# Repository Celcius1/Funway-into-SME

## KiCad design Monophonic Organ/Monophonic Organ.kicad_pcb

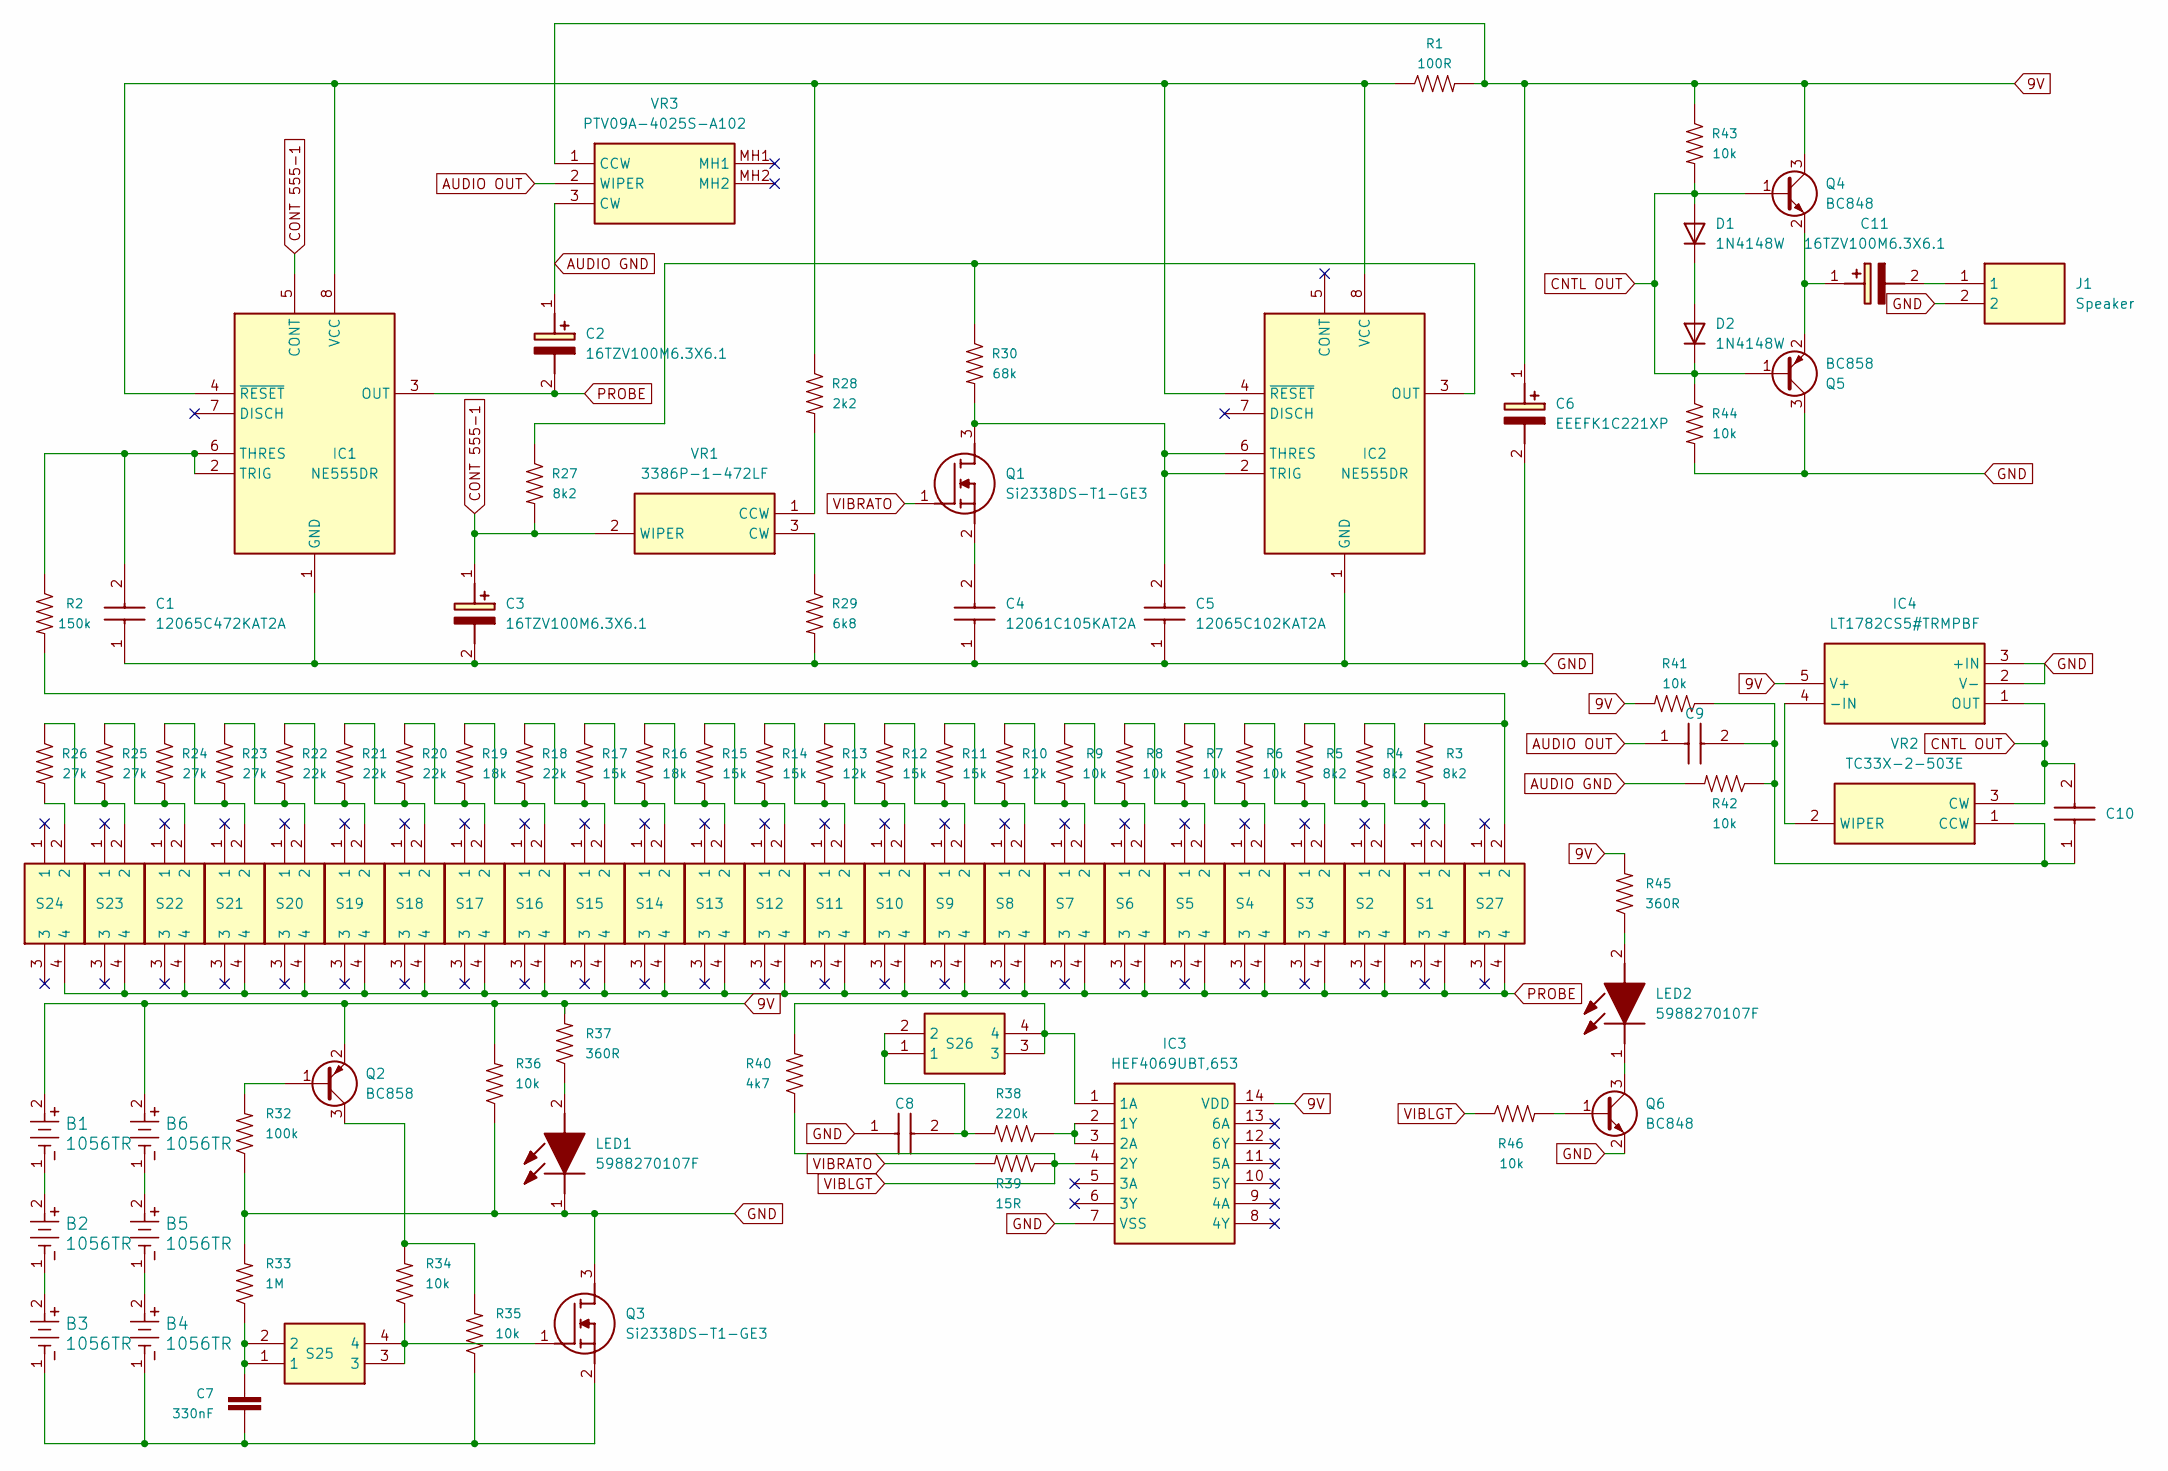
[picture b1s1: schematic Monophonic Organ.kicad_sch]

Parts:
B1, B2, B3, B4, B5, B6: 1056TR
C1: 12065C472KAT2A; CAPC3216X94N; Manufacturer_Part_Number 12065C472KAT2A
C2, C3, C11: 16TZV100M6.3X6.1; 16TZV100M63X61; Manufacturer_Part_Number 16TZV100M6.3X6.1
C4, C9: 12061C105KAT2A; CAPC3216X229N; Manufacturer_Part_Number 12061C105KAT2A
C5: 12065C102KAT2A; CAPC3216X94N; Manufacturer_Part_Number 12065C102KAT2A
C6: EEEFK1C221XP; EEE0JA331XP; Manufacturer_Part_Number EEEFK1C221XP
C7: 330nF; C_1206_3216Metric
C8: 12061C473KAT2A; CAPC3216X94N; Manufacturer_Part_Number 12061C473KAT2A
C10: 12065A150JAT2A; CAPC3216X94N; Manufacturer_Part_Number 12065A150JAT2A
D1, D2: 1N4148W; D_SOD-123
IC1, IC2: NE555DR; SOIC127P600X175-8N; Manufacturer_Part_Number NE555DR; Mouser Part Number 595-NE555DR
IC3: HEF4069UBT,653; SOIC127P600X175-14N; Manufacturer_Part_Number HEF4069UBT,653
IC4: LT1782CS5#TRMPBF; SOT95P280X100-5N; Manufacturer_Part_Number LT1782CS5#TRMPBF
J1: Speaker; 17761192; Manufacturer_Part_Number 1776119-2
LED1, LED2: 5988270107F; Manufacturer_Part_Number 5988270107F
Q1, Q3: Si2338DS-T1-GE3; SOT95P237X112-3N; Manufacturer_Part_Number Si2338DS-T1-GE3
Q2, Q5: BC858; SOT-23
Q4, Q6: BC848; SOT-23
R1: 100R; R_1206_3216Metric
R2: 150k; R_1206_3216Metric
R3, R4, R5, R27: 8k2; R_1206_3216Metric
R6, R7, R8, R9, R34, R35, R36, R41, R42, R43, R44, R46: 10k; R_1206_3216Metric
R10, R13: 12k; R_1206_3216Metric
R11, R12, R14, R15, R17: 15k; R_1206_3216Metric
R16, R19: 18k; R_1206_3216Metric
R18, R20, R21, R22: 22k; R_1206_3216Metric
R23, R24, R25, R26: 27k; R_1206_3216Metric
R28: 2k2; R_1206_3216Metric
R29: 6k8; R_1206_3216Metric
R30: 68k; R_1206_3216Metric
R32: 100k; R_1206_3216Metric
R33: 1M; R_1206_3216Metric
R37, R45: 360R; R_1206_3216Metric
R38: 220k; R_1206_3216Metric
R39: 15R; R_1206_3216Metric
R40: 4k7; R_1206_3216Metric
S1, S2, S3, S4, S5, S6, S7, S8, S9, S10, S11, S12, S13, S14, S15, S16, S17, S18, S19, S20, S21, S22, S23, S24, S25, S26, S27: FSM4JSMATR; Manufacturer_Part_Number FSM4JSMATR
VR1: 3386P-1-472LF; 3386P_1; Manufacturer_Part_Number 3386P-1-472LF
VR2: TC33X-2-503E; TC33X2503E; Manufacturer_Part_Number TC33X-2-503E
VR3: PTV09A-4025S-A102; PTV09A4025SA102; Manufacturer_Part_Number PTV09A-4025S-A102

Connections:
9V: B1.2, B6.2, C6.1 (+), IC3.14 (VDD), IC4.5 (V+), Q2.2 (E), Q4.3 (C), R1.2, R36.2, R37.2, R41.2, R43.1, R45.2, VR3.1 (CCW)
AUDIO GND: C2.1 (+), R42.2, VR3.3 (CW)
AUDIO OUT: C9.1, VR3.2 (WIPER)
CNTL OUT: C10.2, D1.2 (A), D2.1 (K), IC4.1 (OUT), Q4.1 (B), Q5.1 (B), R43.2, R44.1, VR2.3 (CW)
CONT 555-1: C3.1 (+), IC1.5 (CONT), R27.2, VR1.2 (WIPER)
GND: C1.1, C3.2 (-), C4.1, C5.1, C6.2 (-), C8.1, IC1.1 (GND), IC2.1 (GND), IC3.7 (VSS), IC4.2 (V-), IC4.3 (+IN), J1.2, LED1.1 (K), Q3.3 (D), Q5.3 (C), Q6.2 (E), R29.2, R32.1, R33.2, R36.1, R44.2
unnamed: B1.1, B2.2
unnamed: B2.1, B3.2
unnamed: B4.2, B5.1
unnamed: B5.2, B6.1
unnamed: C7.2, R33.1, S25.1, S25.2
unnamed: C8.2, R38.2, S26.1, S26.2
unnamed: C11.1 (+), Q4.2 (E), Q5.2 (E)
unnamed: C11.2 (-), J1.1
unnamed: D1.1 (K), D2.2 (A)
unnamed: C1.2, IC1.2 (TRIG), IC1.6 (THRES), R2.1
unnamed: IC1.4 (~RESET), IC1.8 (VCC), IC2.4 (~RESET), IC2.8 (VCC), R1.1, R28.1
unnamed: IC2.3 (OUT), R27.1, R30.1
unnamed: C5.2, IC2.2 (TRIG), IC2.6 (THRES), Q1.3 (D), R30.2
unnamed: IC3.1 (1A), R40.2, S26.3, S26.4
unnamed: IC3.2 (1Y), IC3.3 (2A), R38.1
unnamed: IC4.4 (-IN), VR2.2 (WIPER)
unnamed: LED1.2 (A), R37.1
unnamed: LED2.2 (A), R45.1
unnamed: LED2.1 (K), Q6.3 (C)
unnamed: C4.2, Q1.2 (S)
unnamed: Q2.1 (B), R32.2
unnamed: Q2.3 (C), R34.2, R35.2
unnamed: Q3.1 (G), R34.1, S25.3, S25.4
unnamed: B3.1, B4.1, C7.1, Q3.2 (S), R35.1
unnamed: Q6.1 (B), R46.2
unnamed: R2.2, R3.1, S27.2
unnamed: R3.2, R4.1, S1.2
unnamed: R4.2, R5.1, S2.2
unnamed: R5.2, R6.1, S3.2
unnamed: R6.2, R7.1, S4.2
unnamed: R7.2, R8.1, S5.2
unnamed: R8.2, R9.1, S6.2
unnamed: R9.2, R10.1, S7.2
unnamed: R10.2, R11.1, S8.2
unnamed: R11.2, R12.1, S9.2
unnamed: R12.2, R13.1, S10.2
unnamed: R13.2, R14.1, S11.2
unnamed: R14.2, R15.1, S12.2
unnamed: R15.2, R16.1, S13.2
unnamed: R16.2, R17.1, S14.2
unnamed: R17.2, R18.1, S15.2
unnamed: R18.2, R19.1, S16.2
unnamed: R19.2, R20.1, S17.2
unnamed: R20.2, R21.1, S18.2
unnamed: R21.2, R22.1, S19.2
unnamed: R22.2, R23.1, S20.2
unnamed: R23.2, R24.1, S21.2
unnamed: R24.2, R25.1, S22.2
unnamed: R25.2, R26.1, S23.2
unnamed: R26.2, S24.2
unnamed: R28.2, VR1.1 (CCW)
unnamed: R29.1, VR1.3 (CW)
unnamed: C9.2, C10.1, R41.1, R42.1, VR2.1 (CCW)
PROBE: C2.2 (-), IC1.3 (OUT), S1.4, S2.4, S3.4, S4.4, S5.4, S6.4, S7.4, S8.4, S9.4, S10.4, S11.4, S12.4, S13.4, S14.4, S15.4, S16.4, S17.4, S18.4, S19.4, S20.4, S21.4, S22.4, S23.4, S24.4, S27.4
VIBLGT: IC3.4 (2Y), R39.1, R40.1, R46.1
VIBRATO: Q1.1 (G), R39.2

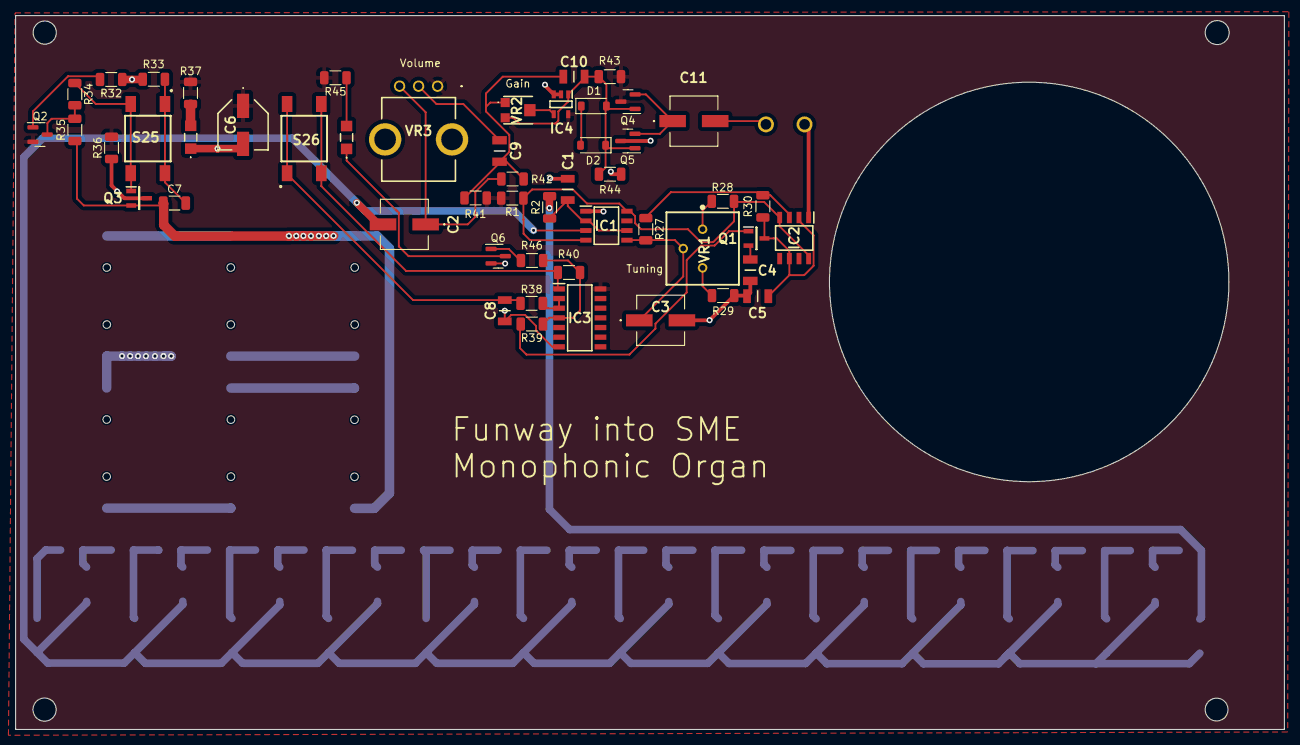
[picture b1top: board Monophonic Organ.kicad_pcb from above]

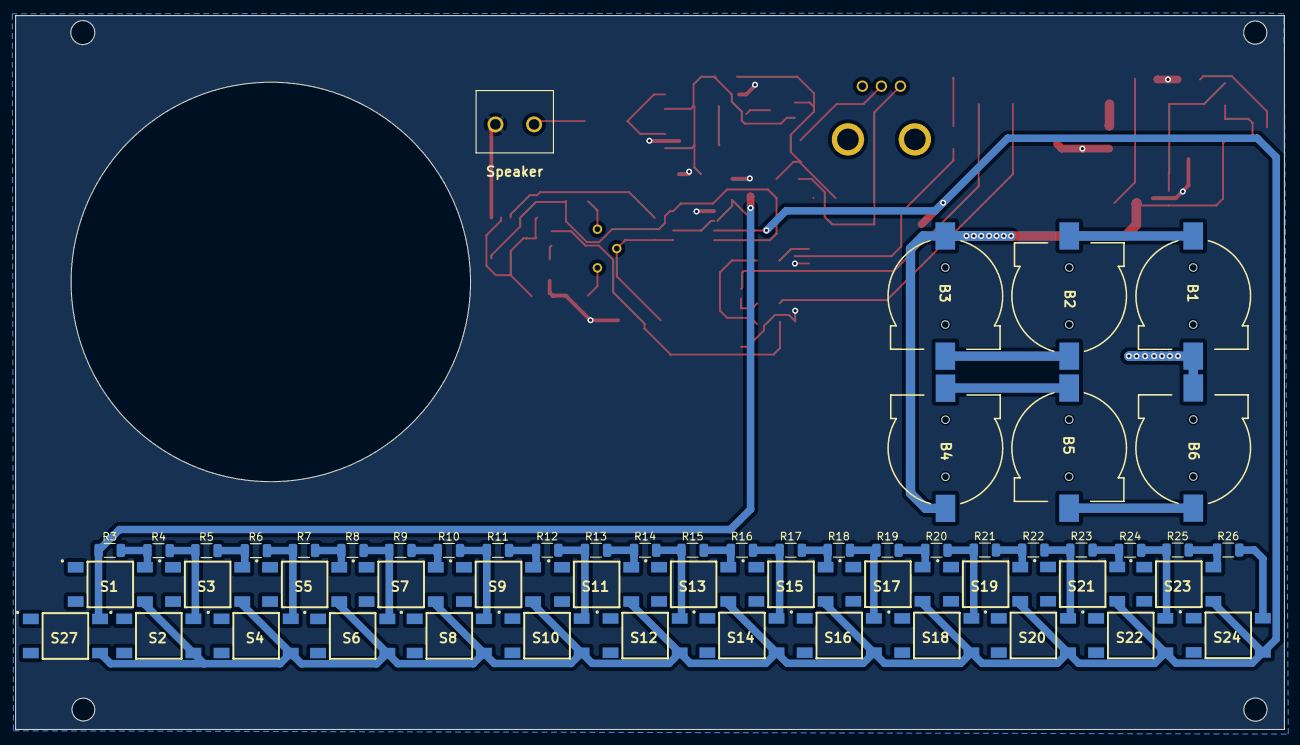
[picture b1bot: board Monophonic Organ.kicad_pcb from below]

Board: 2 copper layers, 166.9 x 93.9 mm, 107 parts (56 on the bottom side), 62 nets.

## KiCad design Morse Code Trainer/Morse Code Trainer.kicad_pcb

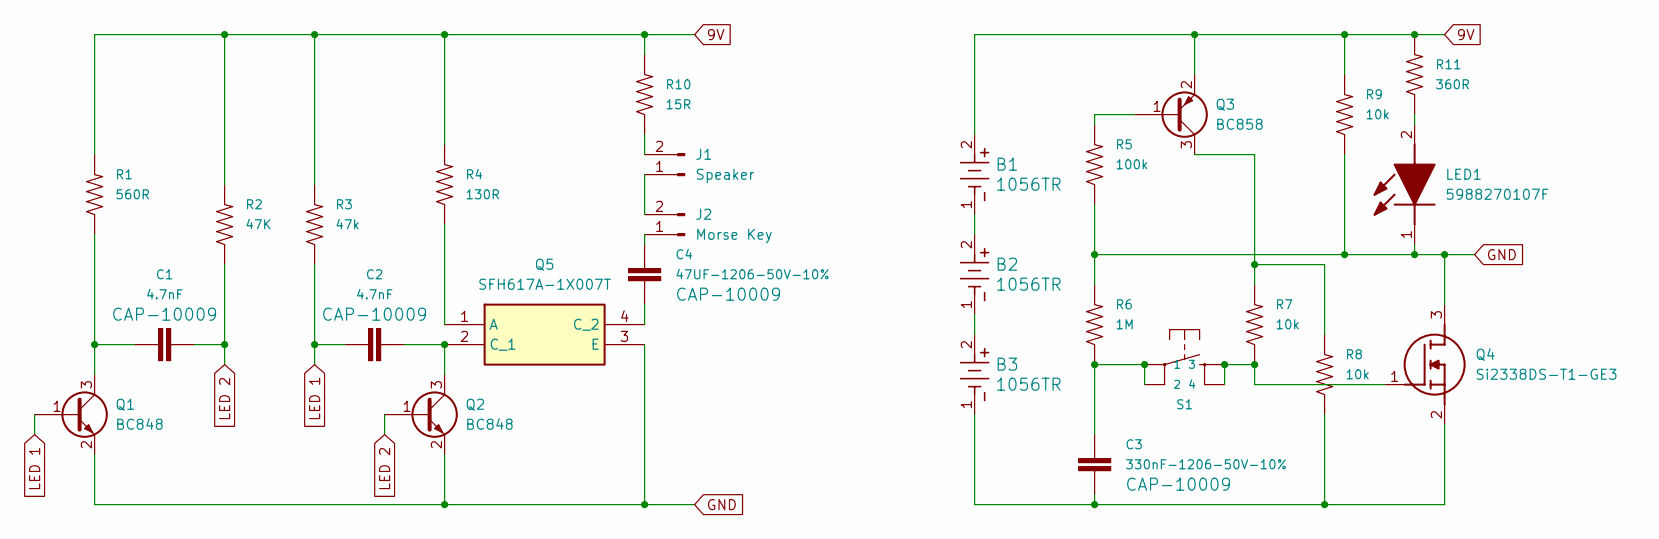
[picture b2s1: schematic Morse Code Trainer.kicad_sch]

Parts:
B1, B2, B3: 1056TR
C1, C2: 4.7nF; C_1206_3216Metric
C3: 330nF-1206-50V-10%; C_1206_3216Metric
C4: 47UF-1206-50V-10%; 1206
J1: Speaker; 17761192
J2: Morse Key; 17761192
LED1: 5988270107F; Manufacturer_Part_Number 5988270107F
Q1, Q2: BC848; SOT-23
Q3: BC858; SOT-23
Q4: Si2338DS-T1-GE3; SOT95P237X112-3N; Manufacturer_Part_Number Si2338DS-T1-GE3
Q5: SFH617A-1X007T; SOP254P1016X440-4N; Manufacturer_Part_Number SFH617A-1X007T
R1: 560R; C_1206_3216Metric
R2: 47K; C_1206_3216Metric
R3: 47k; C_1206_3216Metric
R4: 130R; C_1206_3216Metric
R5: 100k; C_1206_3216Metric
R6: 1M; C_1206_3216Metric
R7, R8, R9: 10k; C_1206_3216Metric
R10: 15R; C_1206_3216Metric
R11: 360R; C_1206_3216Metric
S1: MOMENTARY-SWITCH-SPST-2-SMD-5.2MM; TACTILE_SWITCH_SMD_5.2MM

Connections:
9V: B1.2, Q3.2 (E), R1.2, R2.2, R3.2, R4.2, R9.2, R10.2, R11.2
GND: LED1.1 (K), Q1.2 (E), Q2.2 (E), Q4.3 (D), Q5.3 (E), R5.1, R6.2, R9.1
LED 1: C2.2, Q1.1 (B), R3.1
LED 2: C1.1, Q2.1 (B), R2.1
unnamed: B1.1, B2.2
unnamed: B2.1, B3.2
unnamed: C3.2, R6.1, S1.1, S1.2
unnamed: J1.1, J2.2
unnamed: J1.2, R10.1
unnamed: C4.1, J2.1
unnamed: LED1.2 (A), R11.1
unnamed: C1.2, Q1.3 (C), R1.1
unnamed: C2.1, Q2.3 (C), Q5.2 (C_1)
unnamed: Q3.1 (B), R5.2
unnamed: Q3.3 (C), R7.2, R8.2
unnamed: Q4.1 (G), R7.1, S1.3, S1.4
unnamed: B3.1, C3.1, Q4.2 (S), R8.1
unnamed: Q5.1 (A), R4.1
unnamed: C4.2, Q5.4 (C_2)

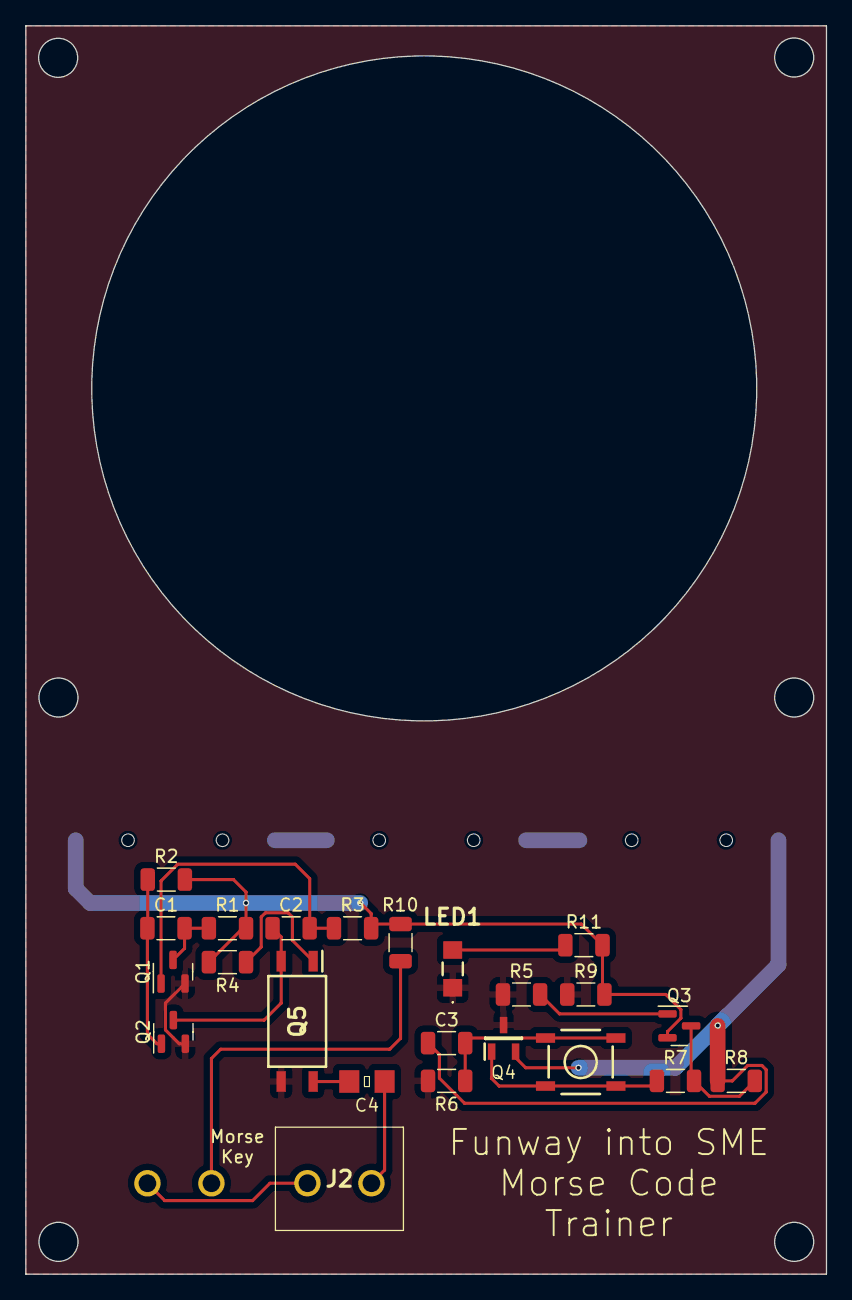
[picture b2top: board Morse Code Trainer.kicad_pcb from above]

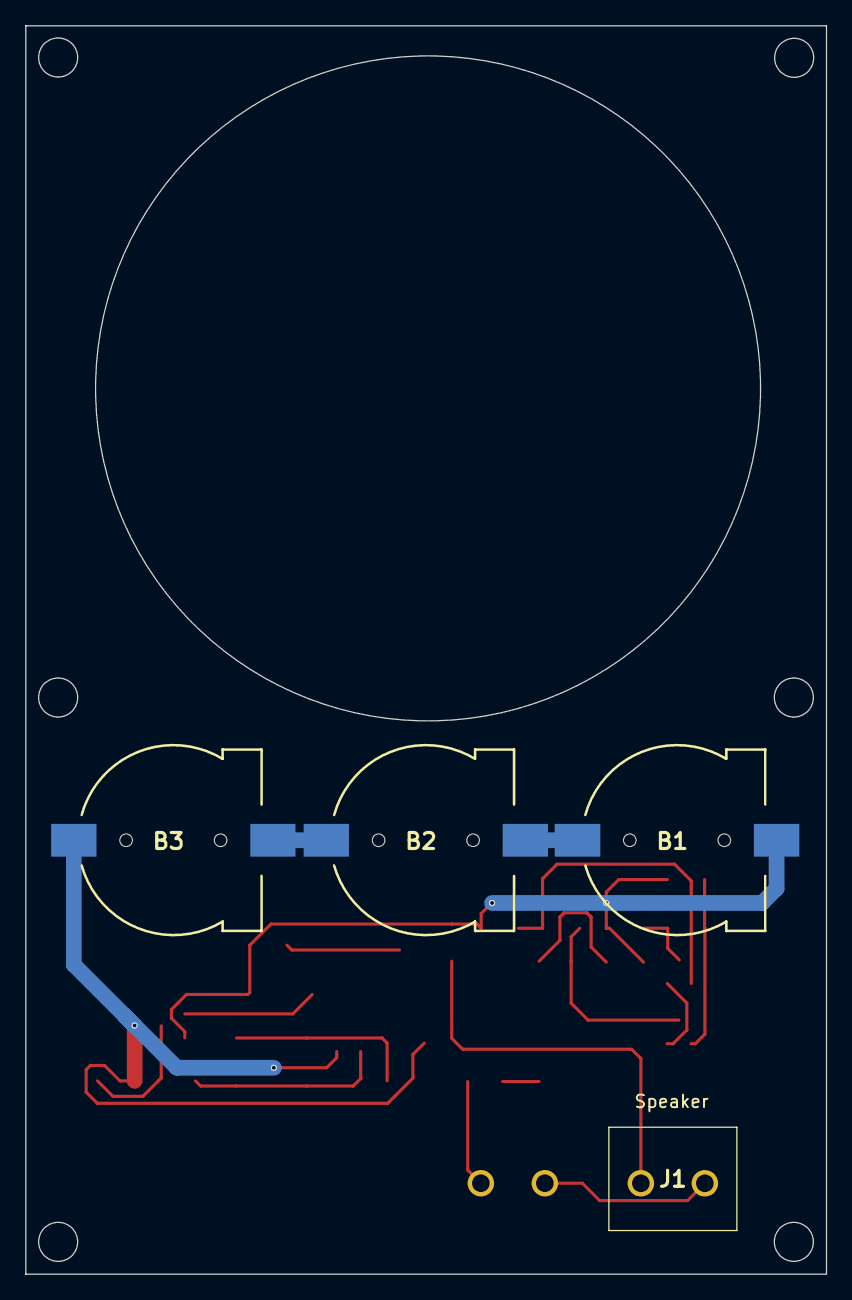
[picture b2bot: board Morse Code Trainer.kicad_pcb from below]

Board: 2 copper layers, 63.6 x 99.1 mm, 27 parts (4 on the bottom side), 19 nets.

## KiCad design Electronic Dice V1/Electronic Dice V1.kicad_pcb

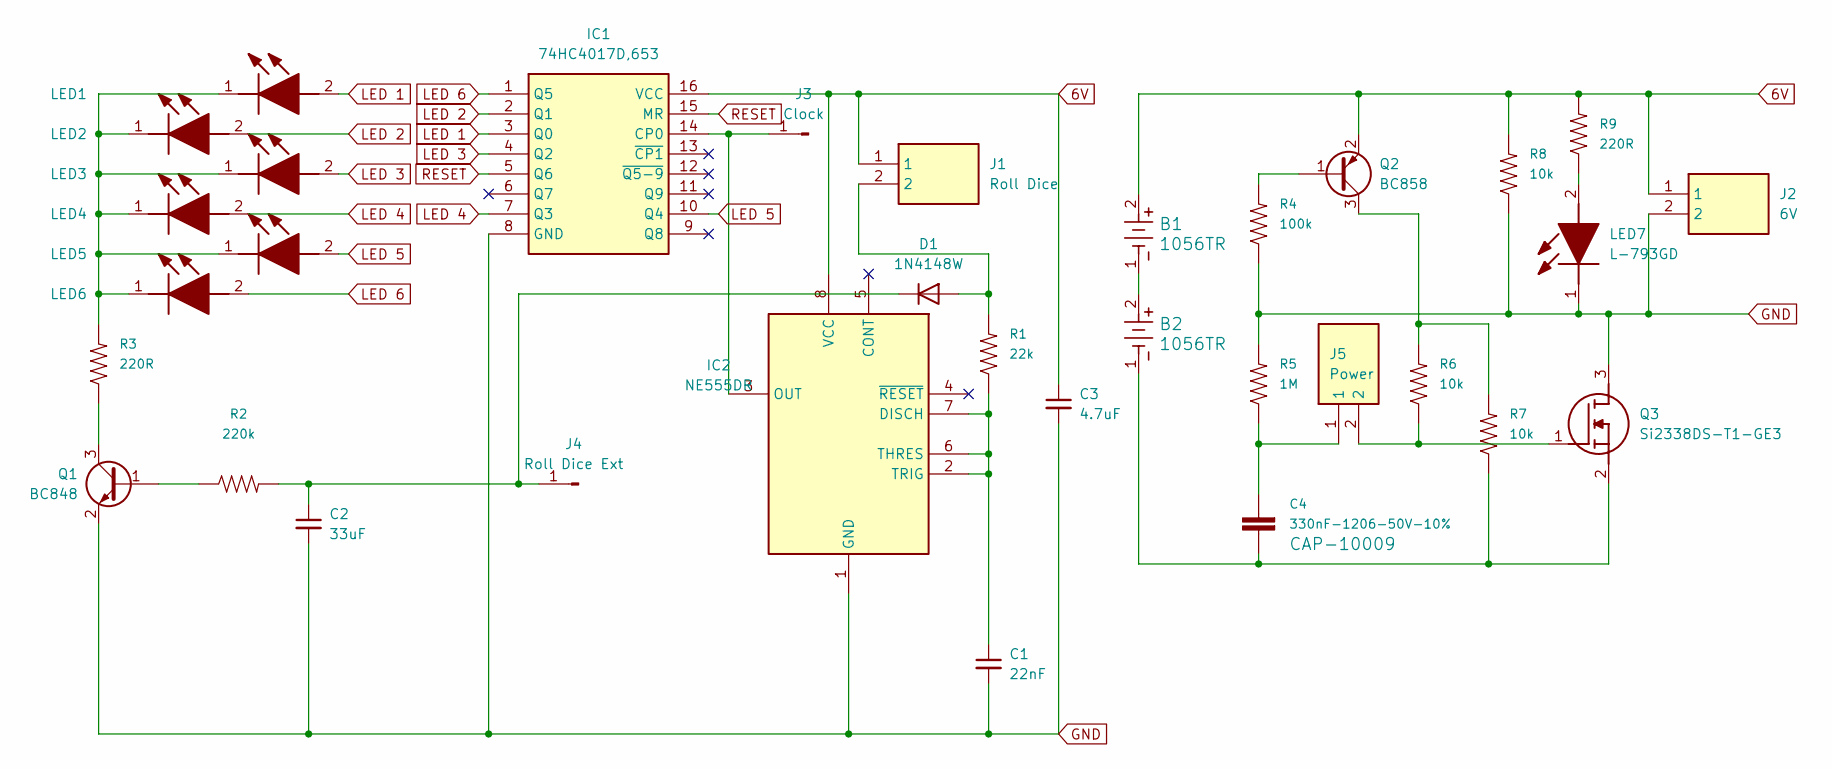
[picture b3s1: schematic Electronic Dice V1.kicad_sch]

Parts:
B1, B2: 1056TR
C1: 22nF; C_1206_3216Metric
C2: 33uF; C_1206_3216Metric
C3: 4.7uF; C_1206_3216Metric
C4: 330nF-1206-50V-10%; C_1206_3216Metric
D1: 1N4148W; D_SOD-123
IC1: 74HC4017D,653; SOIC127P600X175-16N; Manufacturer_Part_Number 74HC4017D,653
IC2: NE555DR; SOIC127P600X175-8N; Manufacturer_Part_Number NE555DR; Mouser Part Number 595-NE555DR
J1: Roll Dice; 17761192; Manufacturer_Part_Number 1776119-2
J2: 6V; 17761192; Manufacturer_Part_Number 1776119-2
J3: Clock; PinHeader_1x01_P2.54mm_Vertical
J4: Roll Dice Ext; PinHeader_1x01_P2.54mm_Vertical
J5: Power; 17761192; Manufacturer_Part_Number 1776119-2
LED1, LED2, LED3, LED4, LED5, LED6, LED7: L-793GD; L793GD; Manufacturer_Part_Number L-793GD
Q1: BC848; SOT-23
Q2: BC858; SOT-23
Q3: Si2338DS-T1-GE3; SOT95P237X112-3N; Manufacturer_Part_Number Si2338DS-T1-GE3
R1: 22k; R_1206_3216Metric
R2: 220k; R_1206_3216Metric
R3, R9: 220R; R_1206_3216Metric
R4: 100k; R_1206_3216Metric
R5: 1M; R_1206_3216Metric
R6, R7, R8: 10k; R_1206_3216Metric

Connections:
6V: B1.2, C3.1, IC1.16 (VCC), IC2.8 (VCC), J1.1, J2.1, Q2.2 (E), R8.2, R9.2
GND: C1.2, C2.2, C3.2, IC1.8 (GND), IC2.1 (GND), J2.2, LED7.1 (K), Q1.2 (E), Q3.3 (D), R4.1, R5.2, R8.1
LED 1: IC1.3 (Q0), LED1.2 (A)
LED 2: IC1.2 (Q1), LED2.2 (A)
LED 3: IC1.4 (Q2), LED3.2 (A)
LED 4: IC1.7 (Q3), LED4.2 (A)
LED 5: IC1.10 (Q4), LED5.2 (A)
LED 6: IC1.1 (Q5), LED6.2 (A)
unnamed: B1.1, B2.2
unnamed: C4.2, J5.1, R5.1
unnamed: D1.2 (A), J1.2, R1.2
unnamed: C2.1, D1.1 (K), J4.1, R2.2
unnamed: IC1.14 (CP0), IC2.3 (OUT), J3.1
unnamed: C1.1, IC2.2 (TRIG), IC2.6 (THRES), IC2.7 (DISCH), R1.1
unnamed: LED1.1 (K), LED2.1 (K), LED3.1 (K), LED4.1 (K), LED5.1 (K), LED6.1 (K), R3.2
unnamed: LED7.2 (A), R9.1
unnamed: Q1.1 (B), R2.1
unnamed: Q1.3 (C), R3.1
unnamed: Q2.1 (B), R4.2
unnamed: Q2.3 (C), R6.2, R7.2
unnamed: J5.2, Q3.1 (G), R6.1
unnamed: B2.1, C4.1, Q3.2 (S), R7.1
RESET: IC1.5 (Q6), IC1.15 (MR)

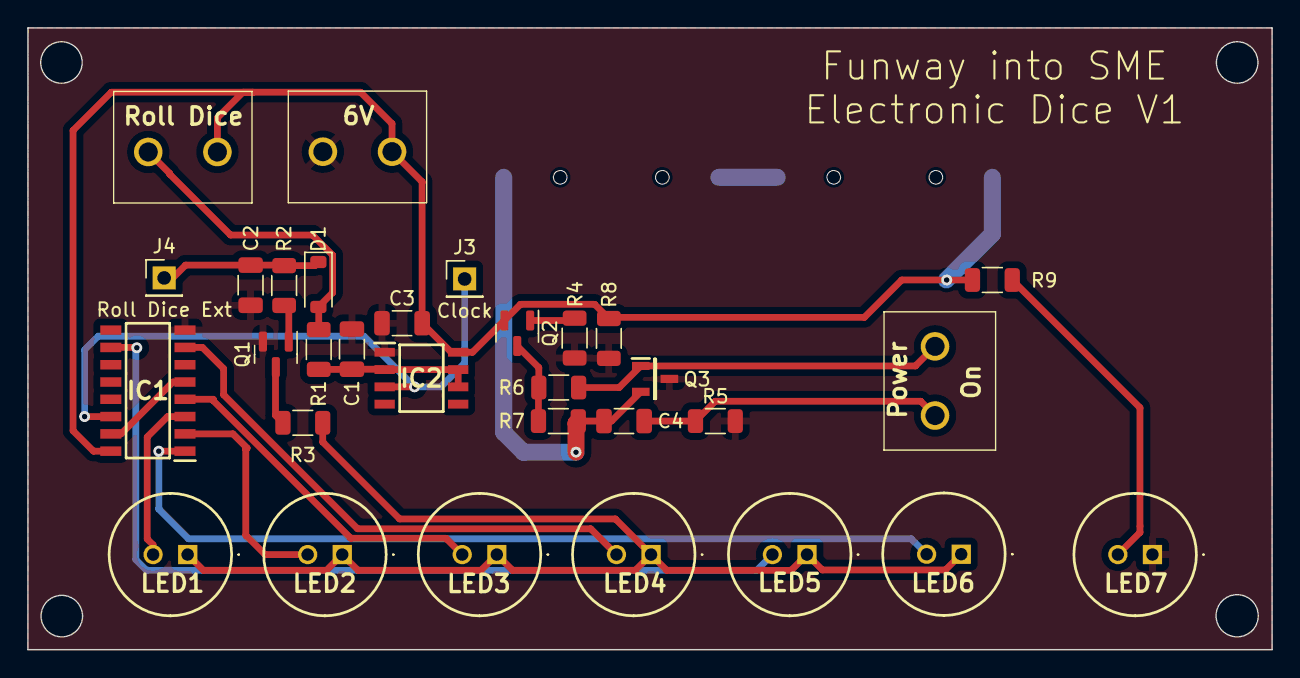
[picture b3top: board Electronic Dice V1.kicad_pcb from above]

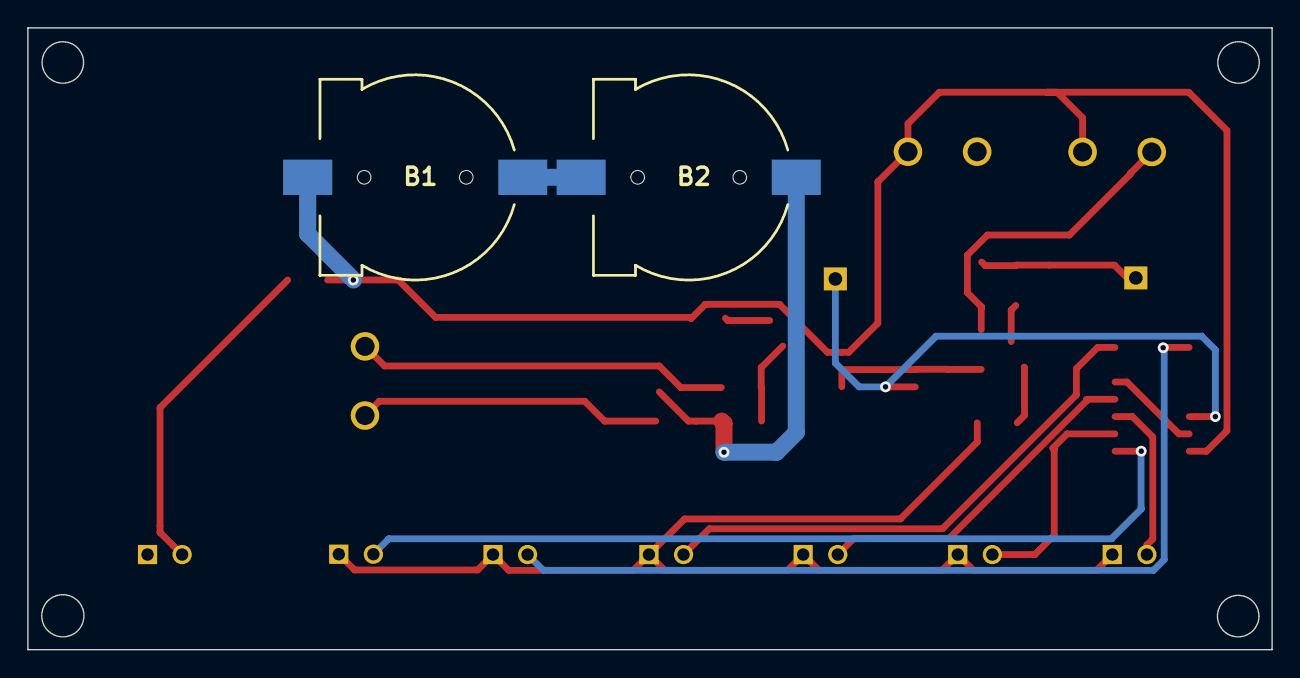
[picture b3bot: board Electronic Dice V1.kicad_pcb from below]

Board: 2 copper layers, 91.4 x 45.7 mm, 33 parts (2 on the bottom side), 23 nets.

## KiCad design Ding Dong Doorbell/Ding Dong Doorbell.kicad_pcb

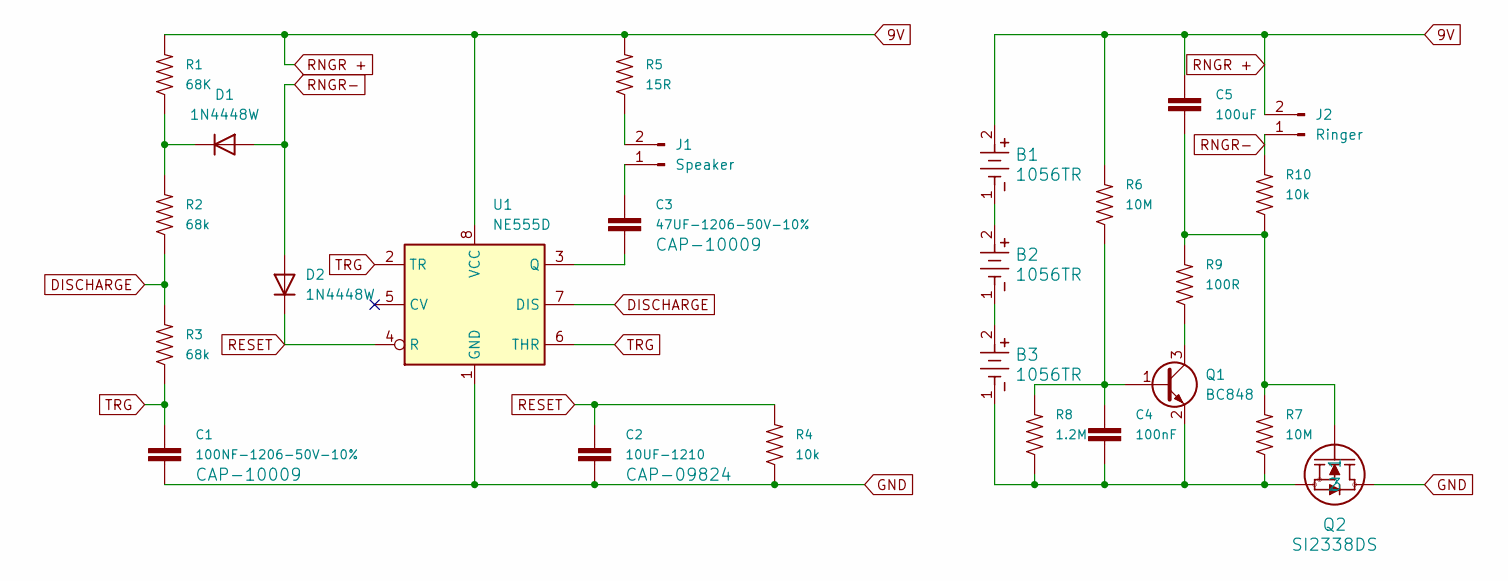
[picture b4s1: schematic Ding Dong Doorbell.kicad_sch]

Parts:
B1, B2, B3: 1056TR; 1048P_KEY
C1: 100NF-1206-50V-10%; 1206
C2: 10UF-1210; 1210
C3: 47UF-1206-50V-10%; 1210
C4: 100nF; C_1206_3216Metric
C5: 100uF; C_1210_3225Metric
D1, D2: 1N4448W; D_SOD-123
J1: Speaker; CONN_1890963_PXC
J2: Ringer; CONN_1890963_PXC
Q1: BC848; SOT-23
Q2: SI2338DS; SI2342DS-T1-GE3
R1: 68K; R_1206_3216Metric
R2, R3: 68k; R_1206_3216Metric
R4, R10: 10k; R_1206_3216Metric
R5: 15R; R_1206_3216Metric
R6, R7: 10M; R_1206_3216Metric
R8: 1.2M; R_1206_3216Metric
R9: 100R; R_1206_3216Metric
U1: NE555D; SOIC-8_3.9x4.9mm_P1.27mm

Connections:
9V: B1.2, C5.2, J2.2, R1.2, R5.2, R6.2, U1.8 (VCC)
DISCHARGE: R2.1, R3.2, U1.7 (DIS)
GND: C1.2, C2.2, Q2.3, R4.1, U1.1 (GND)
unnamed: B1.1, B2.2
unnamed: B2.1, B3.2
unnamed: C5.1, Q2.1, R7.2, R9.2, R10.1
unnamed: D1.1 (K), R1.1, R2.2
unnamed: C3.1, J1.1
unnamed: J1.2, R5.1
unnamed: C4.2, Q1.1 (B), R6.1, R8.2
unnamed: Q1.3 (C), R9.1
unnamed: B3.1, C4.1, Q1.2 (E), Q2.2, R7.1, R8.1
unnamed: C3.2, U1.3 (Q)
RESET: C2.1, D2.1 (K), R4.2, U1.4 (R)
RNGR-: D1.2 (A), D2.2 (A), J2.1, R10.2
TRG: C1.1, R3.1, U1.2 (TR), U1.6 (THR)

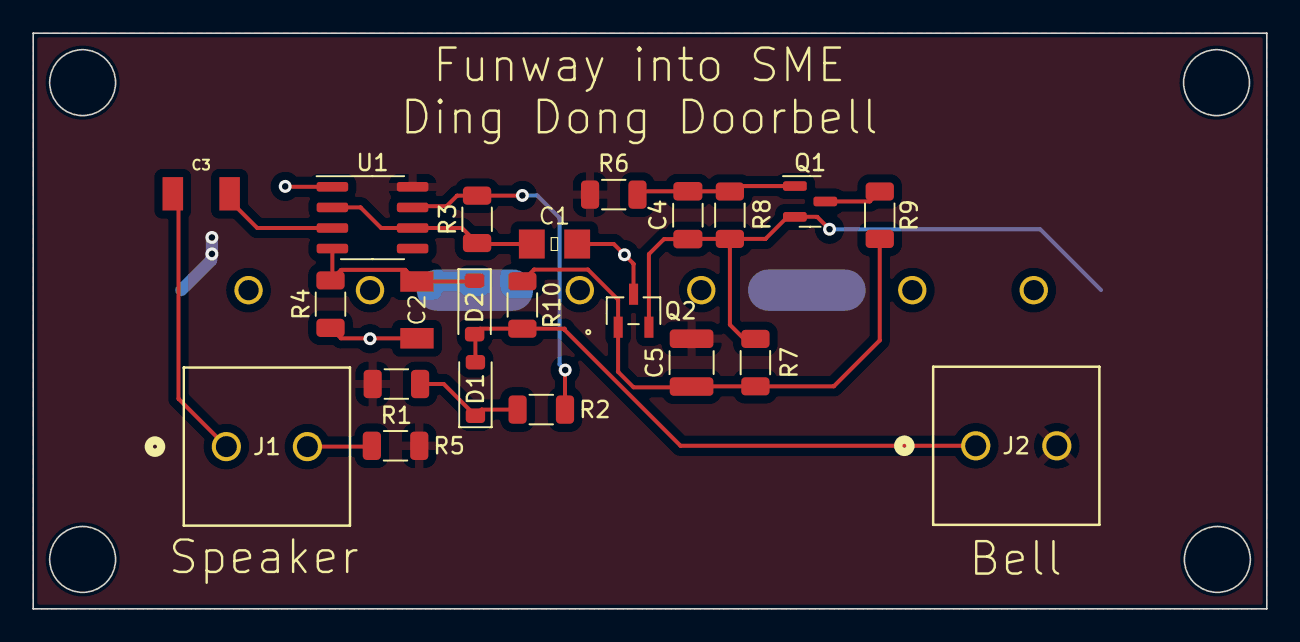
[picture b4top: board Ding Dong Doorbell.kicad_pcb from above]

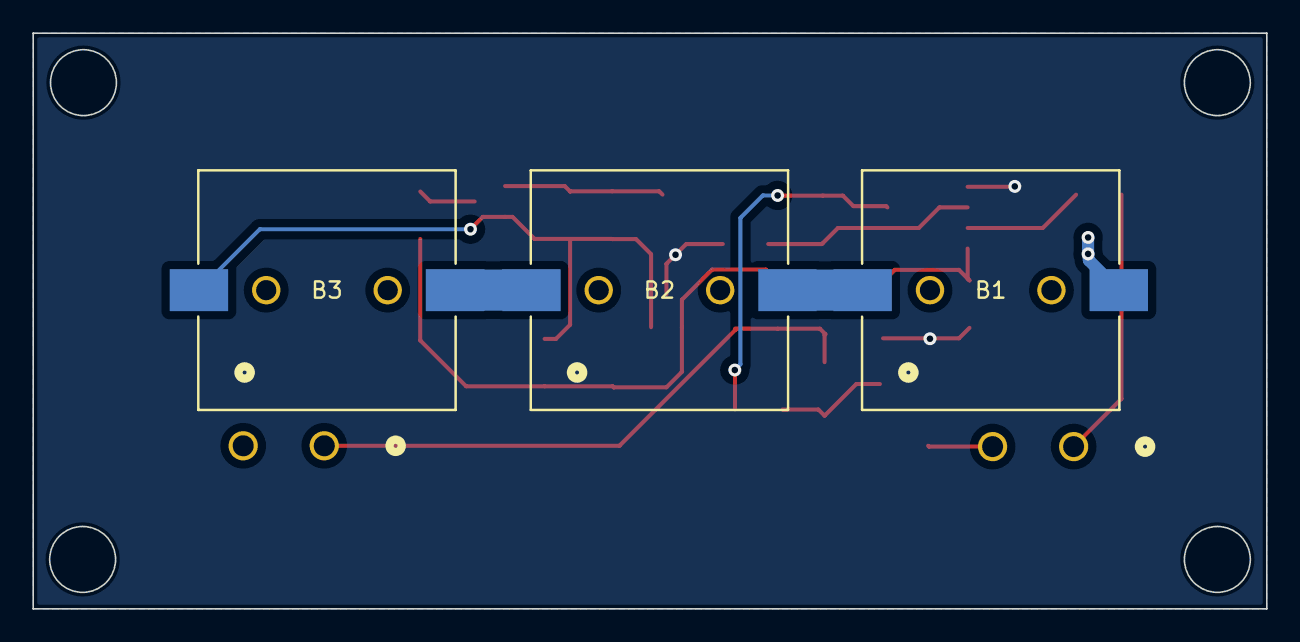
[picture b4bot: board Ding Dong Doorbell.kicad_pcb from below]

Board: 2 copper layers, 76.1 x 35.5 mm, 25 parts (3 on the bottom side), 16 nets.

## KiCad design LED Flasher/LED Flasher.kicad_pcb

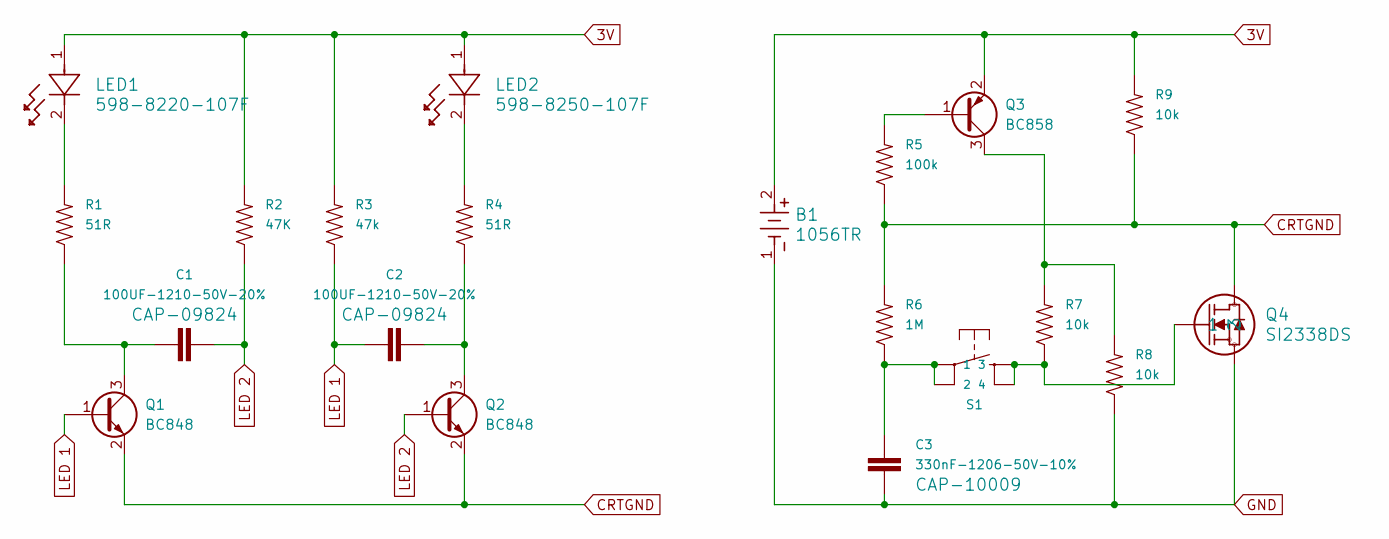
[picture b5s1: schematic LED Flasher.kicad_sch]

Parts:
B1: 1056TR; 1048P_KEY
C1, C2: 100UF-1210-50V-20%; C_1210_3225Metric
C3: 330nF-1206-50V-10%; C_1206_3216Metric
LED1: 598-8220-107F; LED_1206_3216Metric
LED2: 598-8250-107F; LED_1206_3216Metric
Q1, Q2: BC848; SOT-23
Q3: BC858; SOT-23
Q4: SI2338DS; SI2342DS-T1-GE3
R1, R4: 51R; C_1206_3216Metric
R2: 47K; C_1206_3216Metric
R3: 47k; C_1206_3216Metric
R5: 100k; C_1206_3216Metric
R6: 1M; C_1206_3216Metric
R7, R8, R9: 10k; C_1206_3216Metric
S1: MOMENTARY-SWITCH-SPST-2-SMD-5.2MM; TACTILE_SWITCH_SMD_5.2MM

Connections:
3V: B1.2, LED1.1, LED2.1, Q3.2 (E), R2.2, R3.2, R9.2
CRTGND: Q1.2 (E), Q2.2 (E), Q4.3, R5.1, R6.2, R9.1
GND: B1.1, C3.1, Q4.2, R8.1
LED 1: C2.1, Q1.1 (B), R3.1
LED 2: C1.2, Q2.1 (B), R2.1
unnamed: C3.2, R6.1, S1.1, S1.2
unnamed: LED1.2, R1.2
unnamed: LED2.2, R4.2
unnamed: C1.1, Q1.3 (C), R1.1
unnamed: C2.2, Q2.3 (C), R4.1
unnamed: Q3.1 (B), R5.2
unnamed: Q3.3 (C), R7.2, R8.2
unnamed: Q4.1, R7.1, S1.3, S1.4

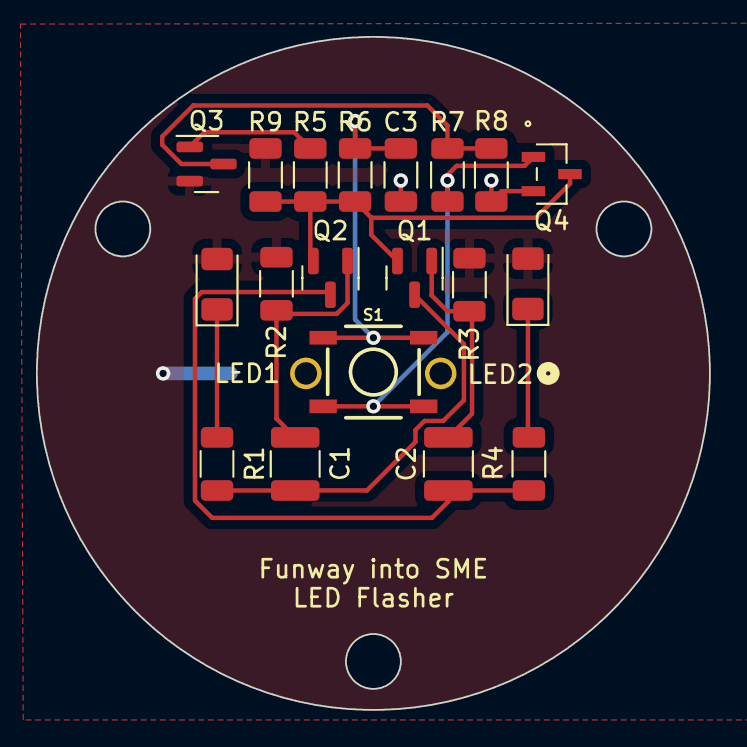
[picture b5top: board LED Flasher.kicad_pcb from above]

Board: 2 copper layers, 37.4 x 37.4 mm, 20 parts (1 on the bottom side), 13 nets.

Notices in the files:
parts and their libraries:
Copyright 2021 Accelerated Designs. All rights reserved.
